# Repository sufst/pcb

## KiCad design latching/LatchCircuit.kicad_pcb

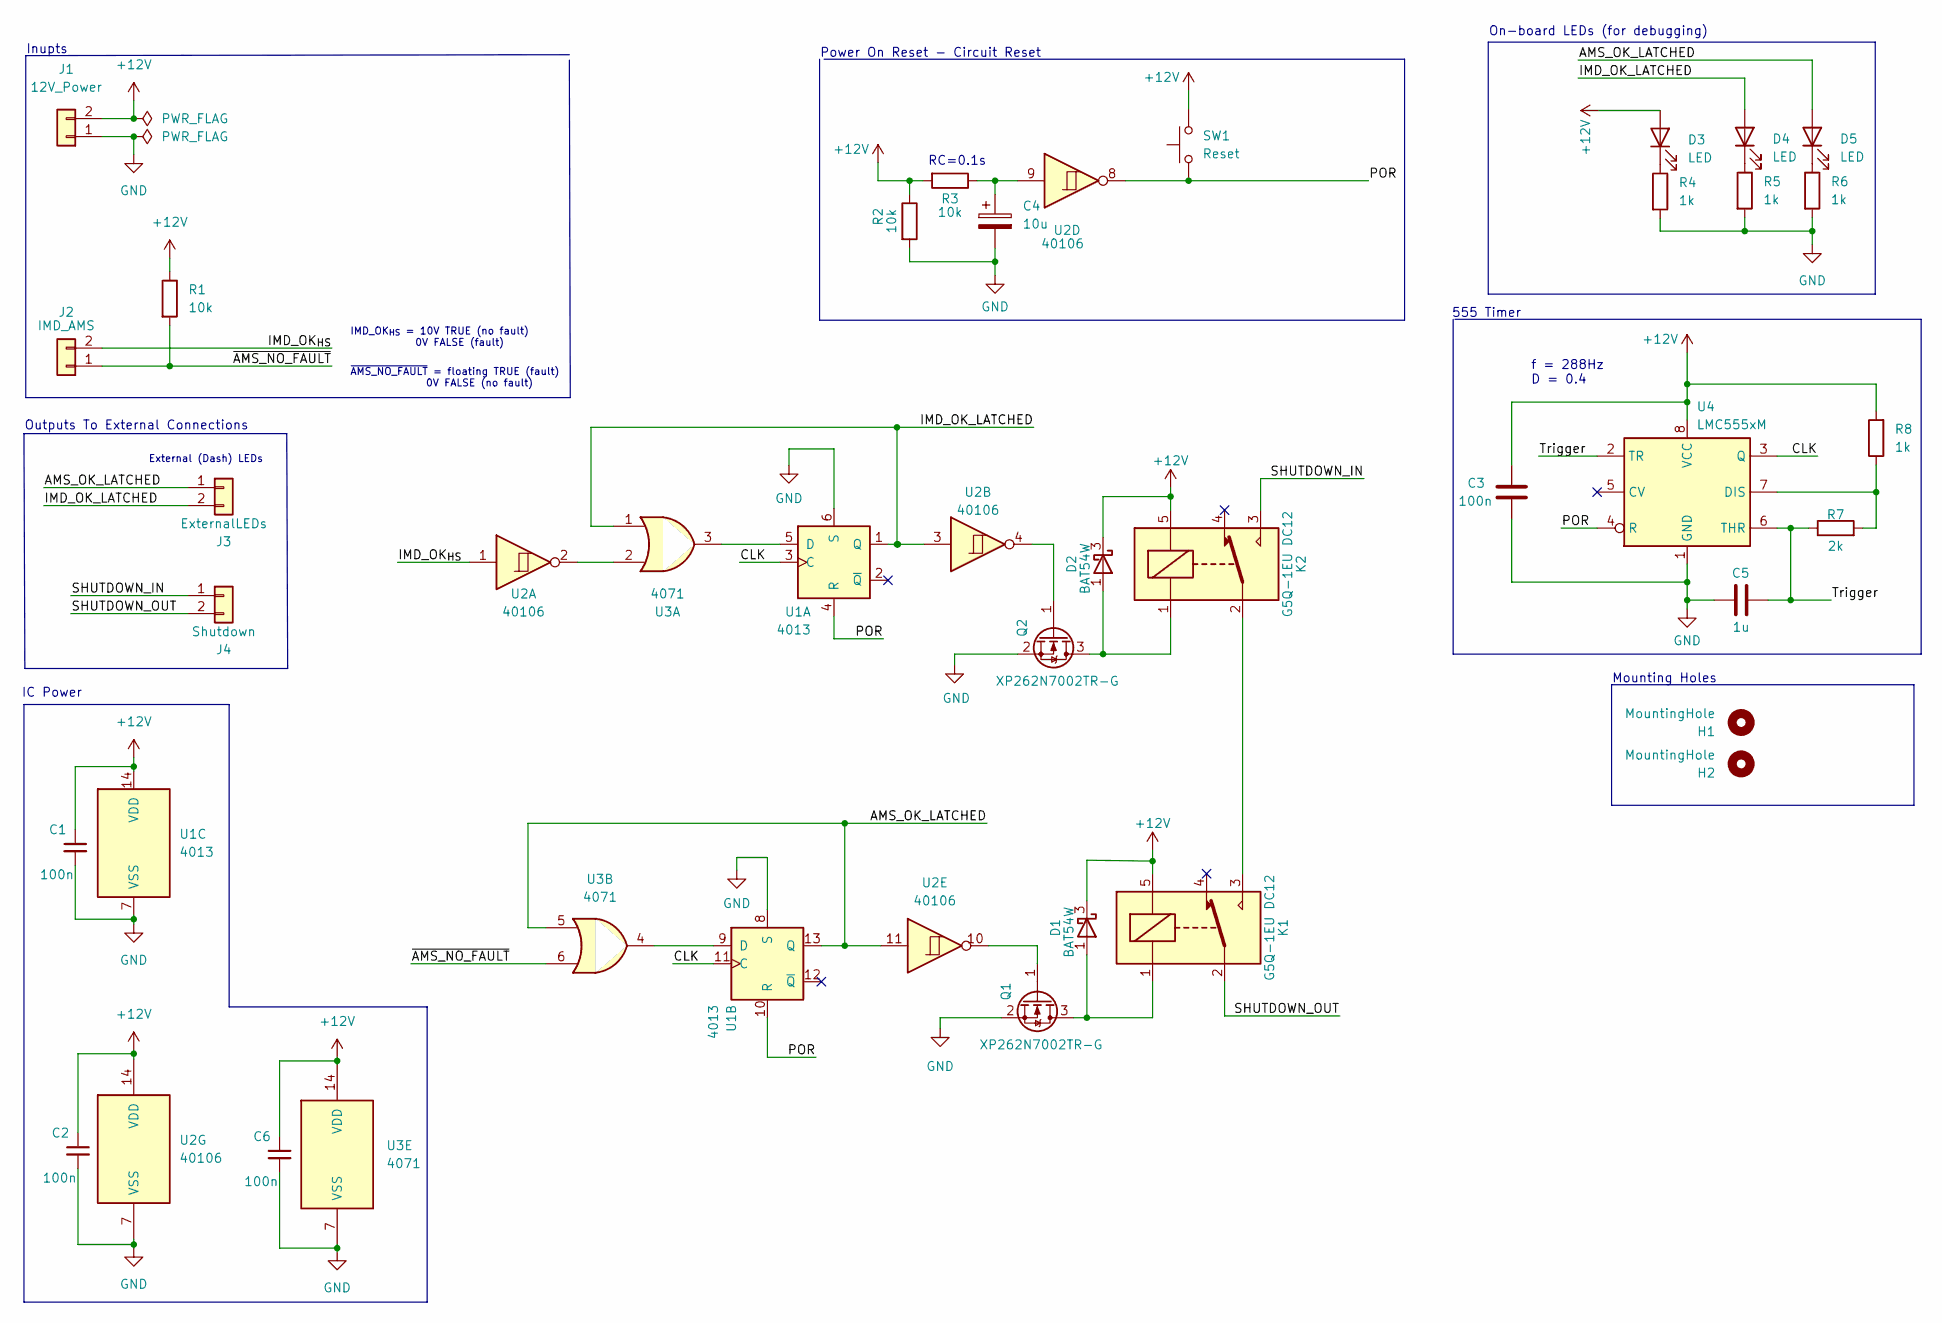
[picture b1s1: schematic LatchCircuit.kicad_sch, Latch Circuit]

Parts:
C1, C2, C3, C6: 100n; C_0603_1608Metric_Pad1.08x0.95mm_HandSolder
C4: 10u; CP_Radial_D5.0mm_P2.00mm
C5: 1u; CP_Radial_D5.0mm_P2.00mm
D1, D2: BAT54W; SOT-323_SC-70
D3, D4, D5: LED; LED_0805_2012Metric_Pad1.15x1.40mm_HandSolder
H1, H2: MountingHole; MountingHole_3.2mm_M3
J1: 12V_Power; Molex_Micro-Fit_3.0_43650-0200_1x02_P3.00mm_Horizontal
J2: IMD_AMS; Molex_Micro-Fit_3.0_43650-0200_1x02_P3.00mm_Horizontal
J3: ExternalLEDs; Molex_Micro-Fit_3.0_43650-0200_1x02_P3.00mm_Horizontal
J4: Shutdown; Molex_Micro-Fit_3.0_43650-0200_1x02_P3.00mm_Horizontal
K1, K2: G5Q-1EU DC12; Relay_SPDT_Omron-G5Q-1
Q1, Q2: XP262N7002TR-G; SOT-23
R1, R2, R3: 10k; R_0603_1608Metric_Pad0.98x0.95mm_HandSolder
R4, R5, R6, R8: 1k; R_0603_1608Metric_Pad0.98x0.95mm_HandSolder
R7: 2k; R_0603_1608Metric_Pad0.98x0.95mm_HandSolder
SW1: Reset; Molex_Micro-Fit_3.0_43650-0200_1x02_P3.00mm_Horizontal
U1: 4013; SOIC-14_3.9x8.7mm_P1.27mm
U2: 40106; SO-14_3.9x8.65mm_P1.27mm
U3: 4071; SOIC-14_3.9x8.7mm_P1.27mm
U4: LMC555xM; SOIC-8_3.9x4.9mm_P1.27mm

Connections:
+12V: C1.1, C2.1, C3.1, C6.1, D1.3 (K), D2.3 (K), D3.2 (A), J1.2, K1.5, K2.5, R1.1, R2.1, R3.2, R8.2, SW1.2, U1.14 (VDD), U2.14 (VDD), U3.14 (VDD), U4.8 (VCC)
/AMS_OK_LATCHED: D5.2 (A), J3.1, U1.13 (Q), U2.11, U3.5
/CLK: U1.3 (C), U1.11 (C), U4.3 (Q)
/IMD_OK_LATCHED: D4.2 (A), J3.2, U1.1 (Q), U2.3, U3.1
/IMD_OK_{HS}: J2.2, U2.1
/POR: SW1.1, U1.4 (R), U1.10 (R), U2.8, U4.4 (R)
/SHUTDOWN_IN: J4.1, K2.3
/SHUTDOWN_OUT: J4.2, K1.2
/Trigger: C5.2, R7.1, U4.2 (TR), U4.6 (THR)
/~AMS_NO_FAULT: J2.1, R1.2, U3.6
GND: C1.2, C2.2, C3.2, C4.2, C5.1, C6.2, J1.1, Q1.2 (S), Q2.2 (S), R2.2, R4.2, R5.2, R6.2, U1.6 (S), U1.7 (VSS), U1.8 (S), U2.7 (VSS), U3.7 (VSS), U4.1 (GND)
unnamed: C4.1, R3.1, U2.9
unnamed: D1.1 (A), K1.1, Q1.3 (D)
unnamed: D2.1 (A), K2.1, Q2.3 (D)
unnamed: D3.1 (K), R4.1
unnamed: D4.1 (K), R5.1
unnamed: D5.1 (K), R6.1
unnamed: K1.3, K2.2
unnamed: Q1.1 (G), U2.10
unnamed: Q2.1 (G), U2.4
unnamed: R7.2, R8.1, U4.7 (DIS)
unnamed: U1.5 (D), U3.3
unnamed: U1.9 (D), U3.4
unnamed: U2.2, U3.2

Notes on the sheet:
555 Timer
External (Dash) LEDs
IMD_OK_{HS} = 10V TRUE (no fault) 0V FALSE (fault)
On-board LEDs (for debugging)
Outputs To External Connections
~{AMS_NO_FAULT} = floating TRUE (fault) 0V FALSE (no fault)
IC Power
Mounting Holes
f = 288Hz D = 0.4
RC=0.1s
Inupts
Power On Reset - Circuit Reset

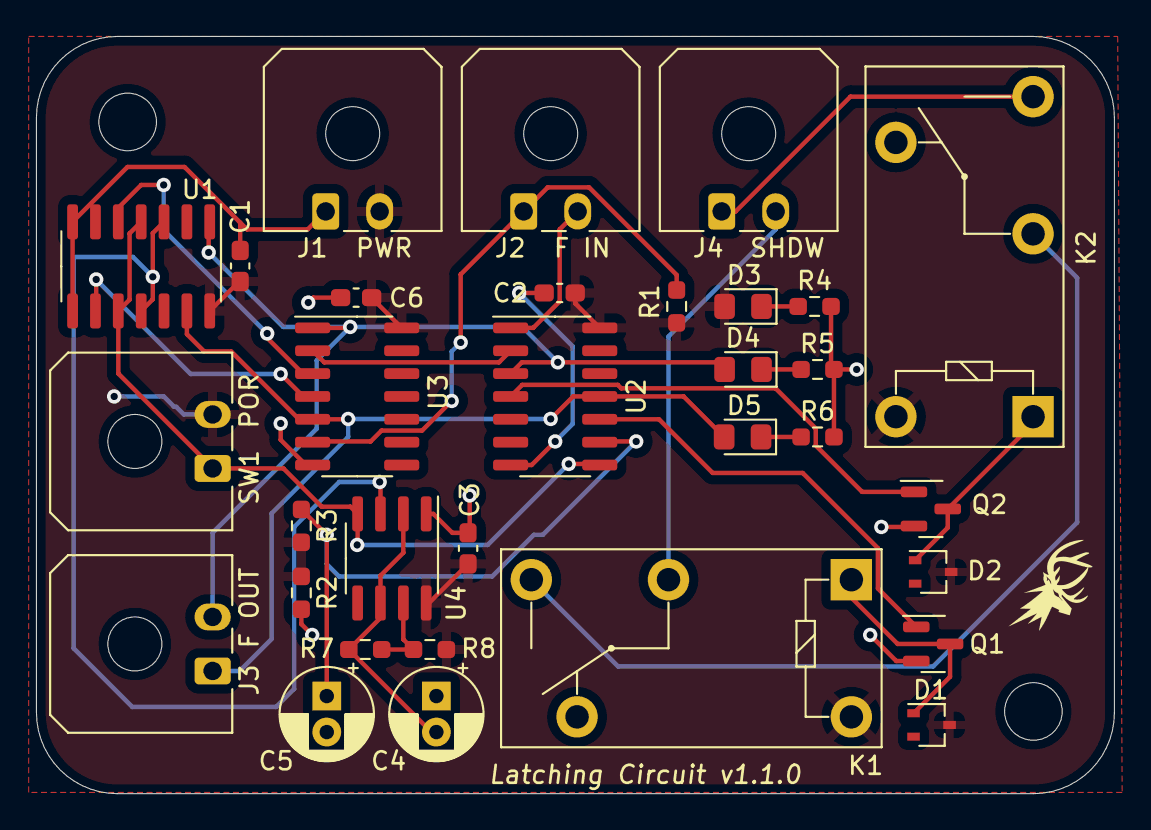
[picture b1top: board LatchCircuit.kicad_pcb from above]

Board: 2 copper layers, 59.9 x 42.1 mm, 34 parts (0 on the bottom side), 24 nets.

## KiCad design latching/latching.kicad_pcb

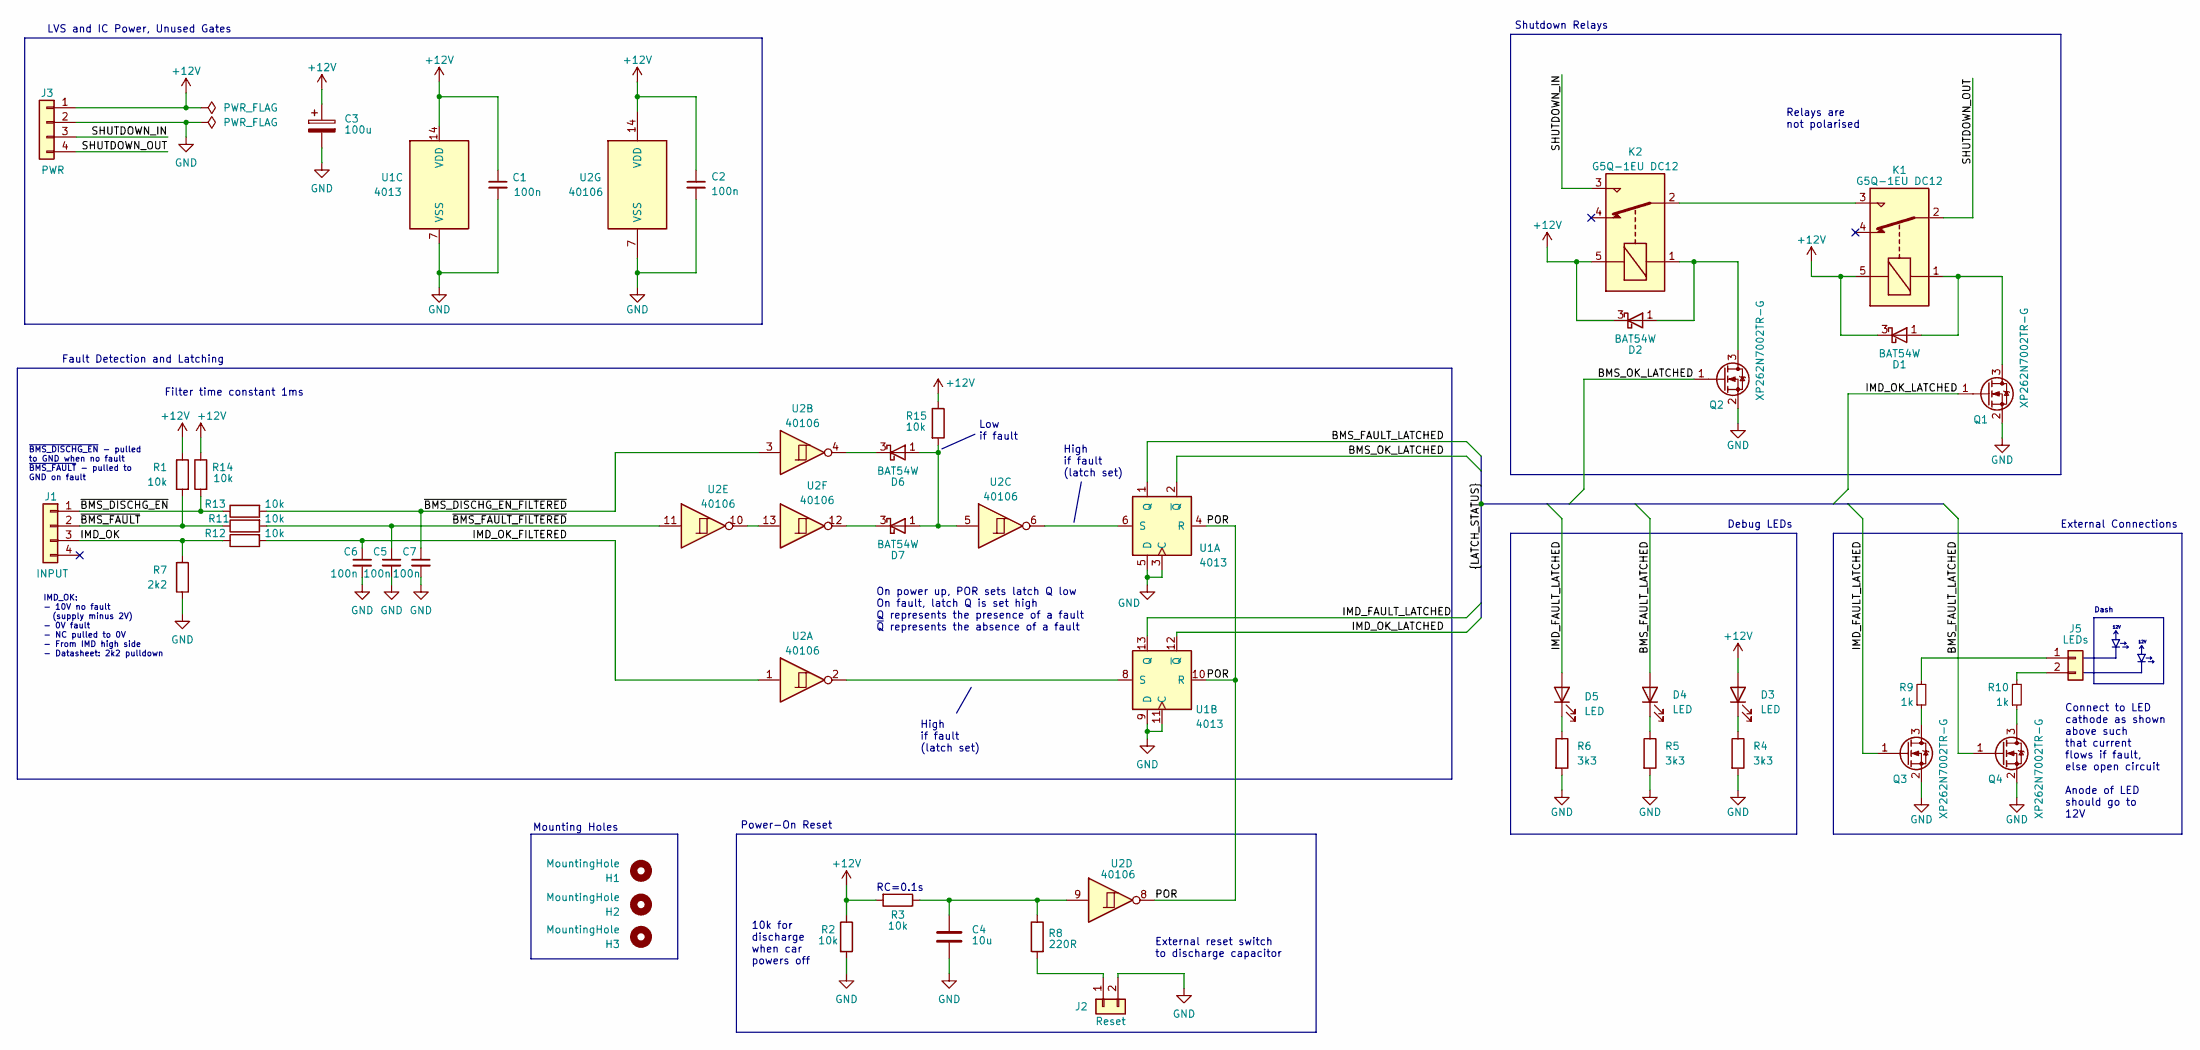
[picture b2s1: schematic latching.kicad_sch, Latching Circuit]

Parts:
C1, C2, C5, C6, C7: 100n; C_0805_2012Metric_Pad1.18x1.45mm_HandSolder
C3: 100u; CP_Radial_D5.0mm_P2.00mm
C4: 10u; C_0805_2012Metric_Pad1.18x1.45mm_HandSolder
D1, D2, D6, D7: BAT54W; SOT-323_SC-70
D3, D4, D5: LED; LED_0805_2012Metric_Pad1.15x1.40mm_HandSolder
H1, H2, H3: MountingHole; MountingHole_3.2mm_M3
J1: INPUT; Molex_Micro-Fit_3.0_43045-0400_2x02_P3.00mm_Horizontal
J2: Reset; Molex_Micro-Fit_3.0_43650-0200_1x02_P3.00mm_Horizontal
J3: PWR; Molex_Micro-Fit_3.0_43045-0400_2x02_P3.00mm_Horizontal
J5: LEDs; Molex_Micro-Fit_3.0_43650-0200_1x02_P3.00mm_Horizontal
K1, K2: G5Q-1EU DC12; Relay_SPDT_Omron-G5Q-1
Q1, Q2, Q3, Q4: XP262N7002TR-G; SOT-23
R1, R2, R3, R11, R12, R13, R14, R15: 10k; R_0805_2012Metric_Pad1.20x1.40mm_HandSolder
R4, R5, R6: 3k3; R_0805_2012Metric_Pad1.20x1.40mm_HandSolder
R7: 2k2; R_0805_2012Metric_Pad1.20x1.40mm_HandSolder
R8: 220R; R_0805_2012Metric_Pad1.20x1.40mm_HandSolder
R9, R10: 1k; R_0805_2012Metric_Pad1.20x1.40mm_HandSolder
U1: 4013; SOIC-14_3.9x8.7mm_P1.27mm
U2: 40106; SOIC-14_3.9x8.7mm_P1.27mm

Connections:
+12V: C1.1, C2.1, C3.1, D1.3 (K), D2.3 (K), D3.2 (A), J3.1, K1.5, K2.5, R1.1, R2.1, R3.2, R14.1, R15.1, U1.14 (VDD), U2.14 (VDD)
/BMS_FAULT_LATCHED: D4.2 (A), Q4.1 (G), U1.1 (Q)
/BMS_OK_LATCHED: Q2.1 (G), U1.2 (~Q)
/IMD_FAULT_LATCHED: D5.2 (A), Q3.1 (G), U1.13 (Q)
/IMD_OK: J1.3, R7.2, R12.1
/IMD_OK_FILTERED: C6.1, R12.2, U2.1
/IMD_OK_LATCHED: Q1.1 (G), U1.12 (~Q)
/POR: U1.4 (R), U1.10 (R), U2.8
/SHUTDOWN_IN: J3.3, K2.3
/SHUTDOWN_OUT: J3.4, K1.2
/~BMS_DISCHG_EN_FILTERED: C7.1, R13.2, U2.3
/~BMS_DISCHG_EN: J1.1, R13.1, R14.2
/~BMS_FAULT_FILTERED: C5.1, R11.2, U2.11
/~BMS_FAULT: J1.2, R1.2, R11.1
GND: C1.2, C2.2, C3.2, C4.2, C5.2, C6.2, C7.2, J2.2, J3.2, Q1.2 (S), Q2.2 (S), Q3.2 (S), Q4.2 (S), R2.2, R4.2, R5.2, R6.2, R7.1, U1.3 (C), U1.5 (D), U1.7 (VSS), U1.9 (D), U1.11 (C), U2.7 (VSS)
unnamed: C4.1, R3.1, R8.1, U2.9
unnamed: D1.1 (A), K1.1, Q1.3 (D)
unnamed: D2.1 (A), K2.1, Q2.3 (D)
unnamed: D3.1 (K), R4.1
unnamed: D4.1 (K), R5.1
unnamed: D5.1 (K), R6.1
unnamed: D6.1 (A), D7.1 (A), R15.2, U2.5
unnamed: D6.3 (K), U2.4
unnamed: D7.3 (K), U2.12
unnamed: J2.1, R8.2
unnamed: J5.1, R9.2
unnamed: J5.2, R10.2
unnamed: K1.3, K2.2
unnamed: Q3.3 (D), R9.1
unnamed: Q4.3 (D), R10.1
unnamed: U1.6 (S), U2.6
unnamed: U1.8 (S), U2.2
unnamed: U2.10, U2.13

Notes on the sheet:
High if fault (latch set)
Shutdown Relays
Connect to LED cathode as shown above such that current flows if fault, else open circuit Anode of LED should go to 12V
Power-On Reset
External Connections
IMD_OK: - 10V no fault (supply minus 2V) - 0V fault - NC pulled to 0V - From IMD high side - Datasheet: 2k2 pulldown
12V
High if fault (latch set)
Debug LEDs
10k for discharge when car powers off
Fault Detection and Latching
Low if fault
~{BMS_DISCHG_EN} - pulled to GND when no fault ~{BMS_FAULT} - pulled to GND on fault
Relays are not polarised
Mounting Holes
Dash
RC=0.1s
On power up, POR sets latch Q low On fault, latch Q is set high Q represents the presence of a fault ~{Q} represents the absence of a fault
LVS and IC Power, Unused Gates
External reset switch to discharge capacitor
Filter time constant 1ms

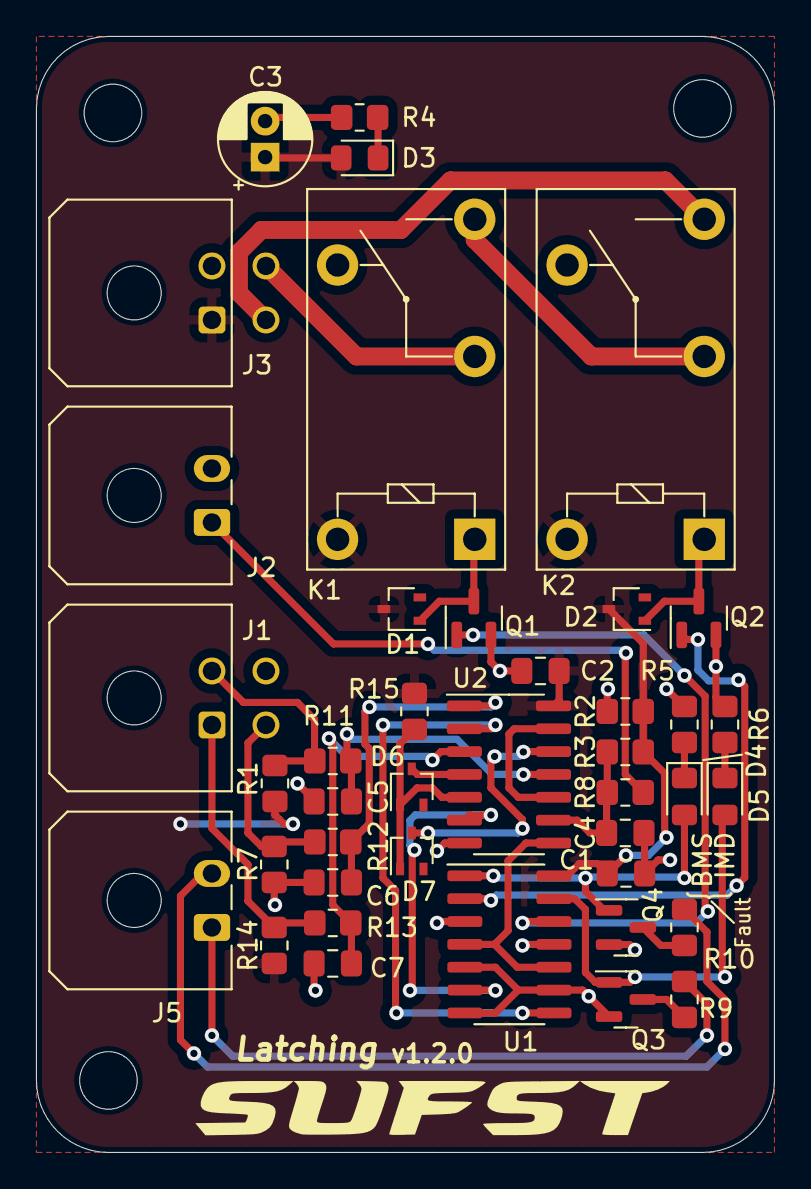
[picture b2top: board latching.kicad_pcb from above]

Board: 2 copper layers, 41.0 x 62.0 mm, 44 parts (0 on the bottom side), 33 nets.

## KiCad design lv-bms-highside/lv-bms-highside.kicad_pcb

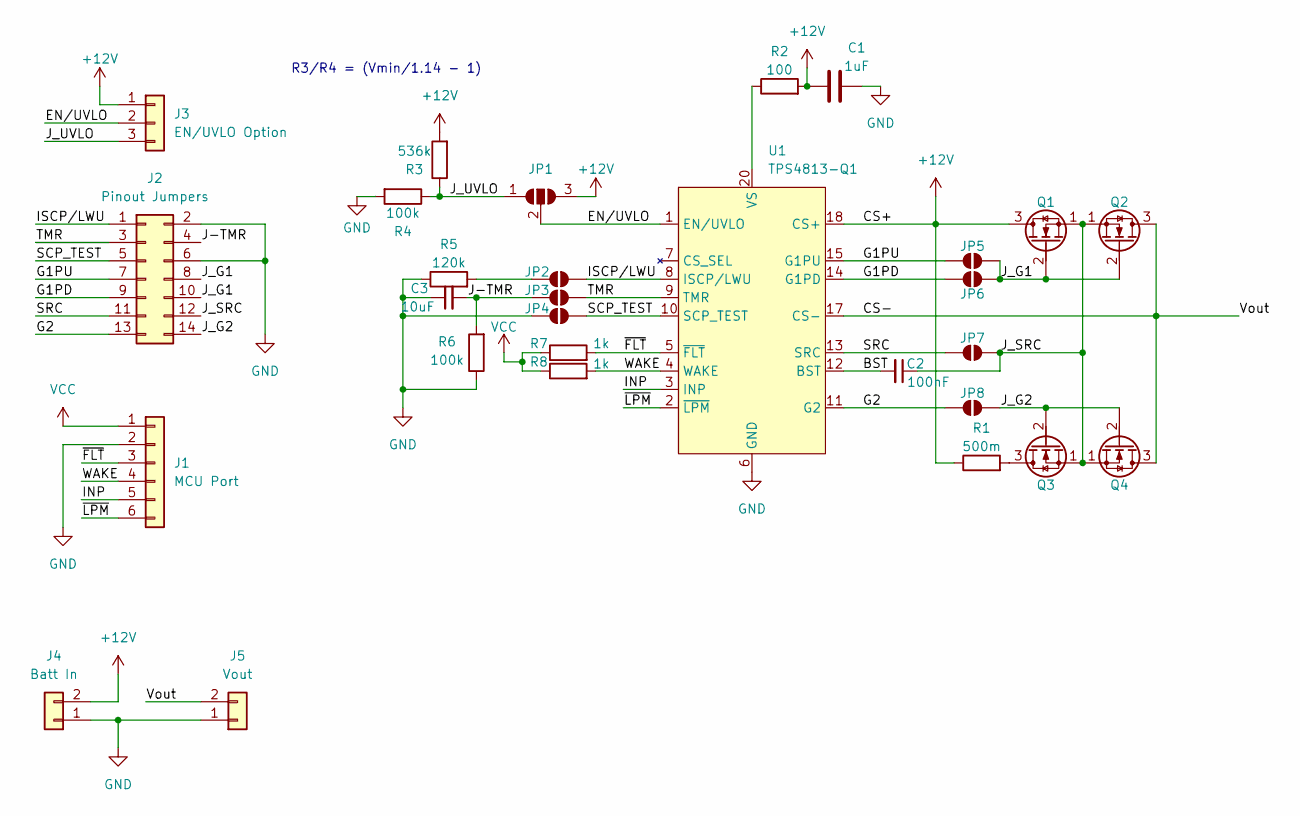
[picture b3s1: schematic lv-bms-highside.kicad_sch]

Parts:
C1: 1uF; C_0805_2012Metric
C2: 100nF; C_0805_2012Metric
C3: 10uF; C_0805_2012Metric
J1: MCU Port; PinHeader_1x06_P2.54mm_Vertical
J2: Pinout Jumpers; PinHeader_2x07_P2.54mm_Vertical
J3: EN/UVLO Option; PinHeader_1x03_P2.54mm_Vertical
J4: Batt In; TerminalBlock_Phoenix_MKDS-1,5-2-5.08_1x02_P5.08mm_Horizont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
J5: Vout; TerminalBlock_Phoenix_MKDS-1,5-2-5.08_1x02_P5.08mm_Horizont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
JP1: SolderJumper_3_Open; SolderJumper-3_P1.3mm_Open_RoundedPad1.0x1.5mm_NumberLabels
JP2, JP3, JP4, JP5, JP6, JP7, JP8: SolderJumper-2_P1.3mm_Open_RoundedPad1.0x1.5mm
Q1, Q2, Q3, Q4: Q_NMOS; DFN3333
R1: 500m; R_2512_6332Metric_Pad1.40x3.35mm_HandSolder
R2: 100; R_0805_2012Metric
R3: 536k; R_0805_2012Metric
R4, R6: 100k; R_0805_2012Metric
R5: 120k; R_0805_2012Metric
R7, R8: 1k; R_0805_2012Metric
U1: TPS4813-Q1; DGX0019A-MFG

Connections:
+12V: C1.2, J3.1, J4.2, JP1.3 (B), Q1.3 (D), R1.1, R2.2, R3.2, U1.18 (CS+)
/BST: C2.2, U1.12 (BST)
/CS-: J5.2, Q2.3 (D), Q4.3 (D), U1.17 (CS-)
/EN/UVLO: J3.2, JP1.2 (C), U1.1 (EN/UVLO)
/G1PD: J2.9, JP6.1 (A), U1.14 (G1PD)
/G1PU: J2.7, JP5.1 (A), U1.15 (G1PU)
/G2: J2.13, JP8.1 (A), U1.11 (G2)
/INP: J1.5, U1.3 (INP)
/ISCP/LWU: J2.1, JP2.2 (B), U1.8 (ISCP/LWU)
/J-TMR: C3.2, J2.4, JP3.1 (A), R6.2
/J_G1: J2.8, J2.10, JP5.2 (B), JP6.2 (B), Q1.2 (G), Q2.2 (G)
/J_G2: J2.14, JP8.2 (B), Q3.2 (G), Q4.2 (G)
/J_SRC: C2.1, J2.12, JP7.2 (B), Q1.1 (S), Q2.1 (S), Q3.1 (S), Q4.1 (S)
/J_UVLO: J3.3, JP1.1 (A), R3.1, R4.1
/SCP_TEST: J2.5, JP4.2 (B), U1.10 (SCP_TEST)
/SRC: J2.11, JP7.1 (A), U1.13 (SRC)
/TMR: J2.3, JP3.2 (B), U1.9 (TMR)
/WAKE: J1.4, R8.2, U1.4 (WAKE)
/~FLT: J1.3, R7.2, U1.5 (~FLT)
/~LPM: J1.6, U1.2 (~LPM)
GND: C1.1, C3.1, J1.2, J2.2, J2.6, J4.1, J5.1, JP4.1 (A), R4.2, R5.1, R6.1, U1.6 (GND)
unnamed: JP2.1 (A), R5.2
unnamed: Q3.3 (D), R1.2
unnamed: R2.1, U1.20 (VS)
VCC: J1.1, R7.1, R8.1

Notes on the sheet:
R3/R4 = (Vmin/1.14 - 1)

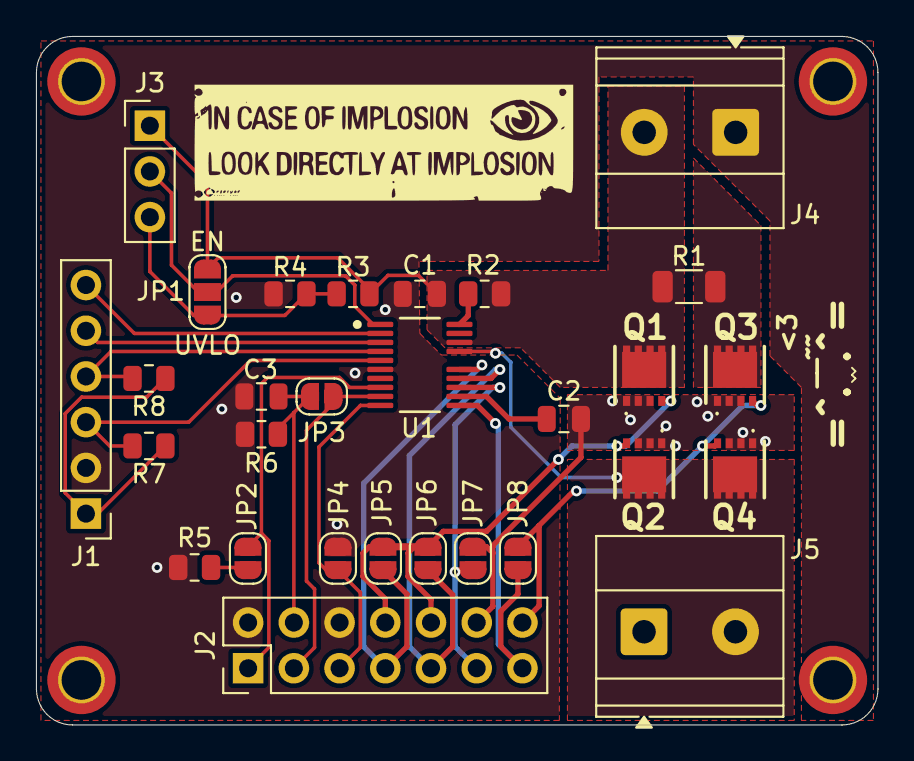
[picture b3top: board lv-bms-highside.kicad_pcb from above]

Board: 2 copper layers, 46.8 x 38.2 mm, 29 parts (0 on the bottom side), 25 nets.

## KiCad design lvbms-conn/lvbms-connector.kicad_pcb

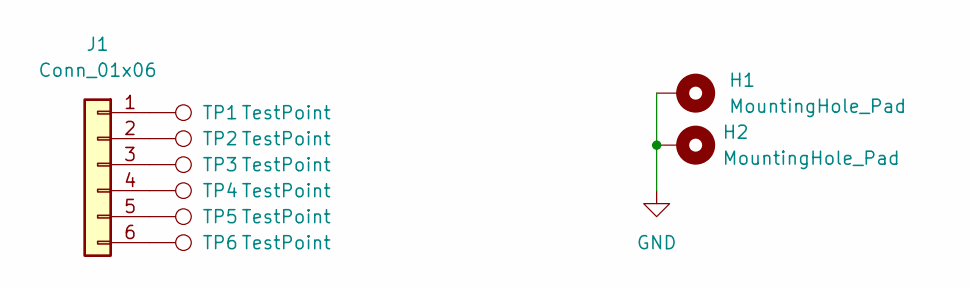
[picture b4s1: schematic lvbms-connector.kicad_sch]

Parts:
H1, H2: MountingHole_Pad; MountingHole_3.2mm_M3_DIN965_Pad_TopBottom
J1: Conn_01x06; Molex_Micro-Fit_3.0_43650-0600_1x06_P3.00mm_Horizontal
TP1, TP2, TP3, TP4, TP5, TP6: TestPoint; TestPoint_Pad_D1.0mm

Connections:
GND: H1.1, H2.1
unnamed: J1.1, TP1.1
unnamed: J1.2, TP2.1
unnamed: J1.3, TP3.1
unnamed: J1.4, TP4.1
unnamed: J1.5, TP5.1
unnamed: J1.6, TP6.1

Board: 2 copper layers, 9 parts (0 on the bottom side), 7 nets, no tracks yet.

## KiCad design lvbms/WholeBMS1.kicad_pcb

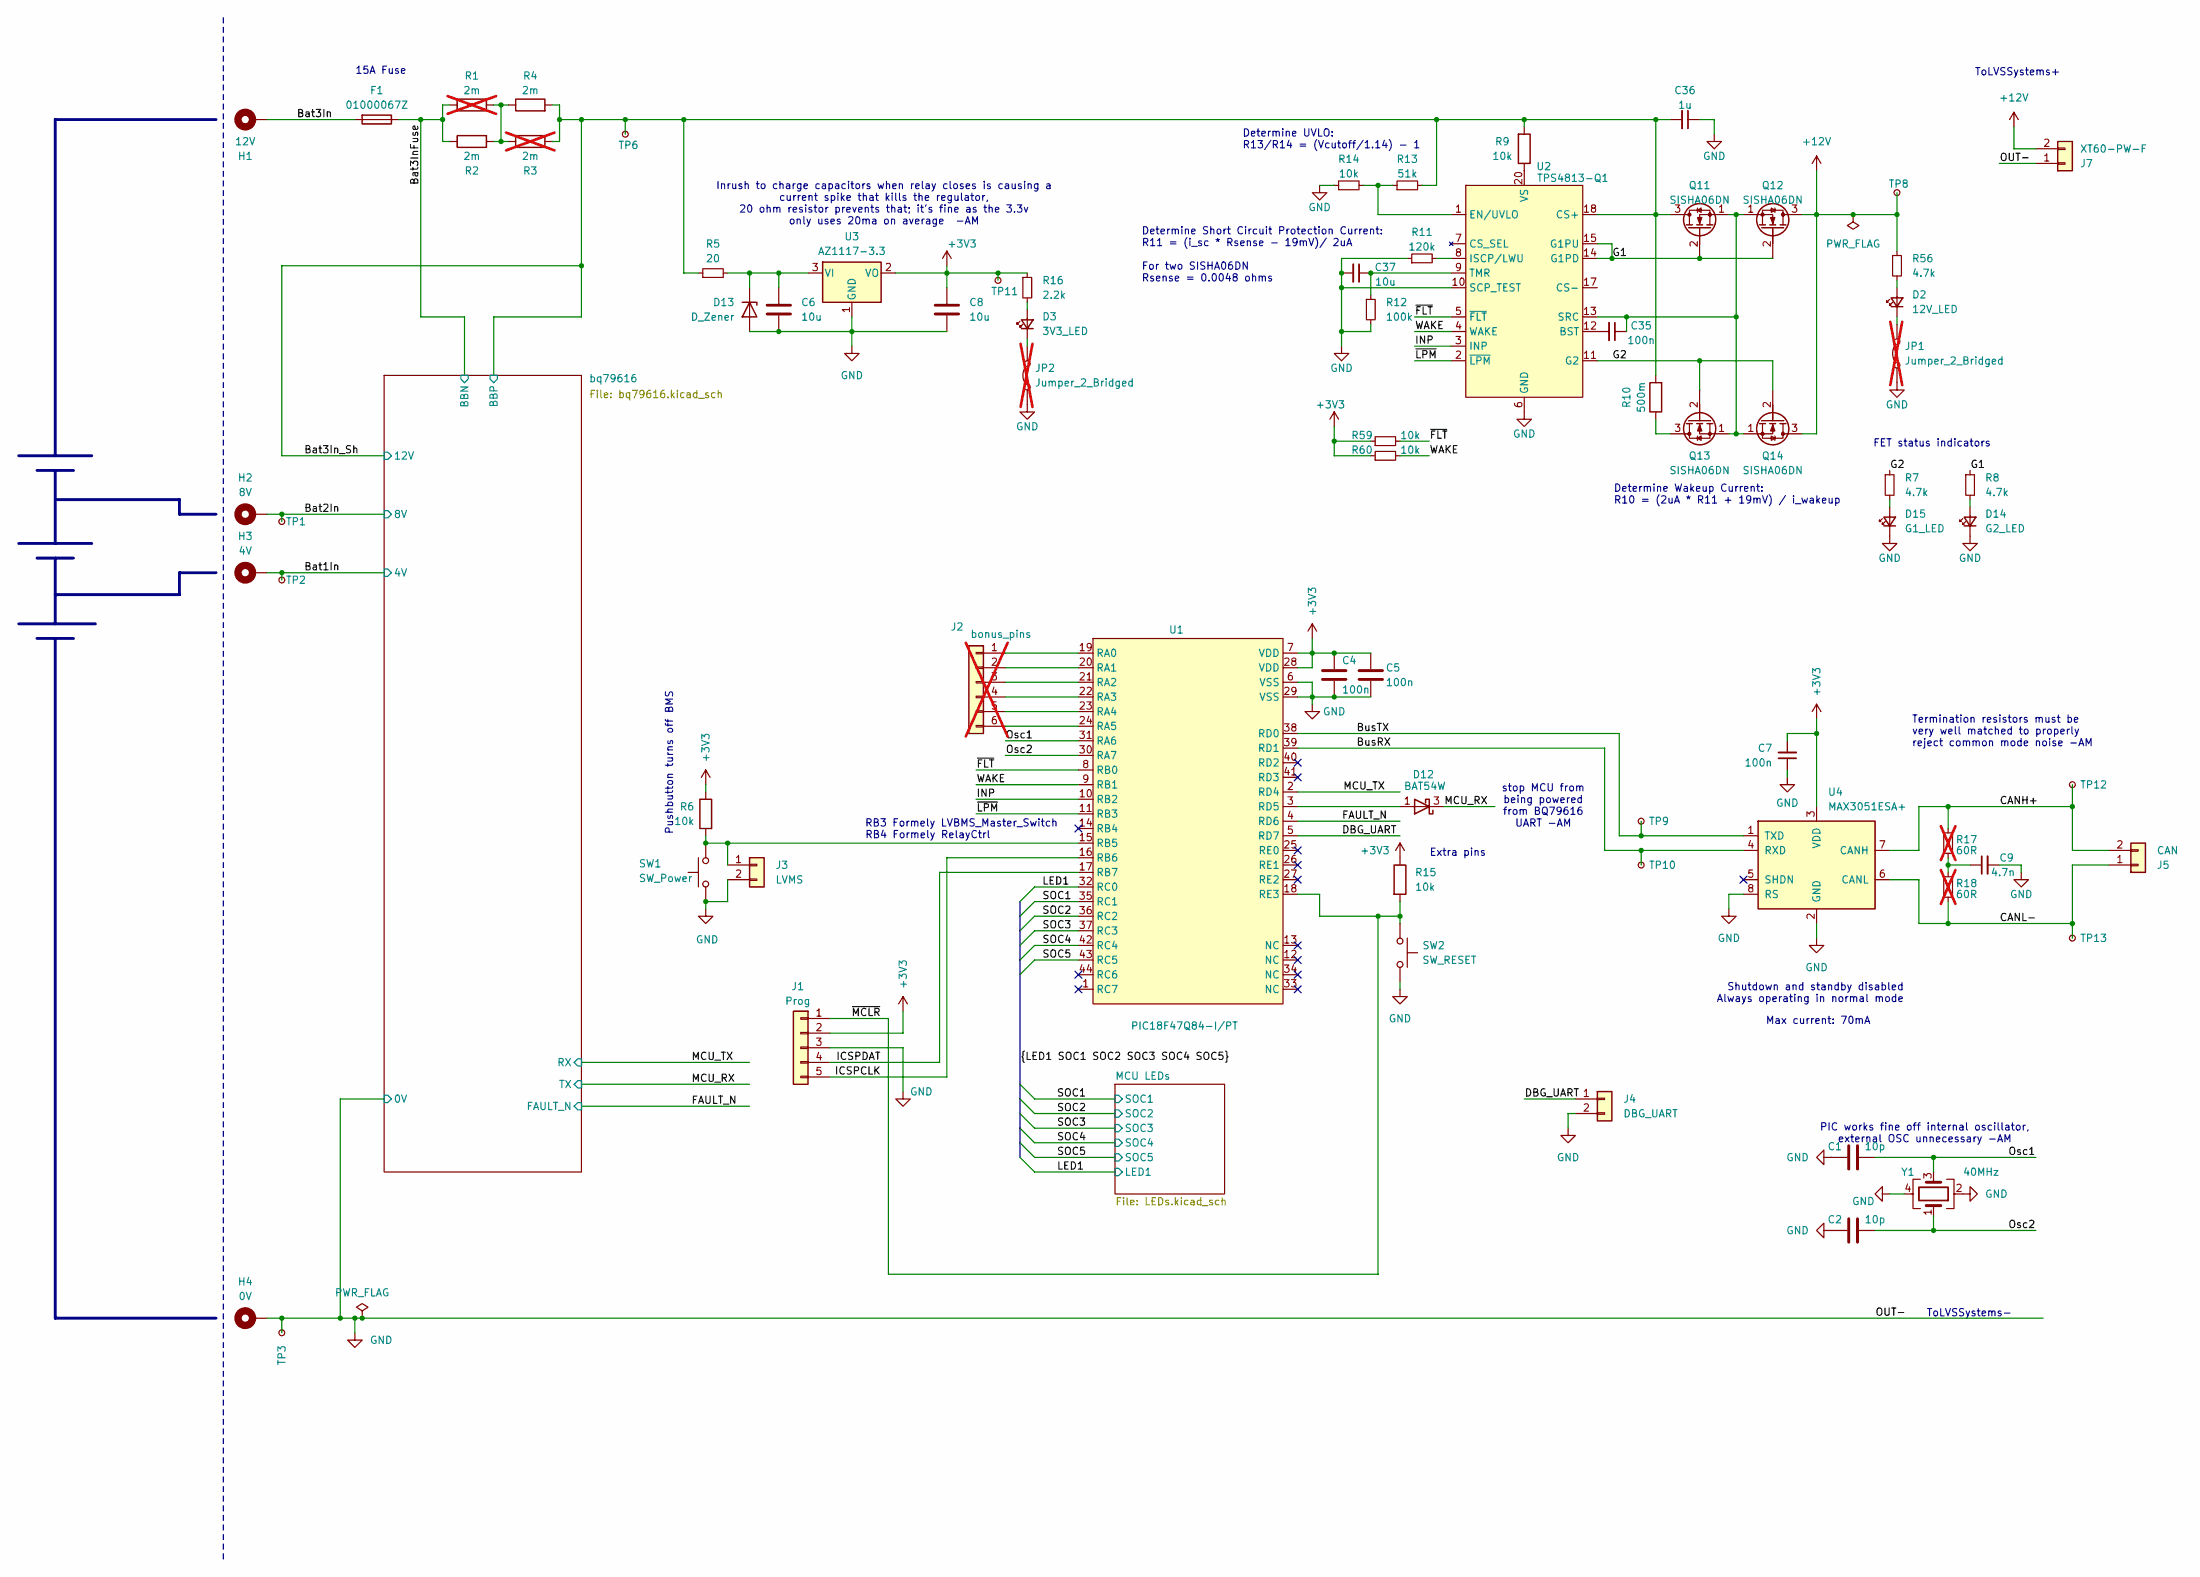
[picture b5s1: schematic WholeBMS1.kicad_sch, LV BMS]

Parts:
C1, C2: 10p; C_0603_1608Metric
C4, C5, C7, C35: 100n; C_0603_1608Metric
C6, C8, C37: 10u; C_0603_1608Metric
C9: 4.7n; C_0603_1608Metric
C36: 1u; C_0603_1608Metric
D2: 12V_LED; LED_0805_2012Metric_Pad1.15x1.40mm_HandSolder
D3: 3V3_LED; LED_0805_2012Metric_Pad1.15x1.40mm_HandSolder
D12: BAT54W; SOT-323_SC-70
D13: D_Zener; D_SOD-123
D14: G2_LED; LED_0805_2012Metric_Pad1.15x1.40mm_HandSolder
D15: G1_LED; LED_0805_2012Metric_Pad1.15x1.40mm_HandSolder
F1: 01000067Z; 01000060Z
H1: 12V; MountingHole_3.2mm_M3_Pad_TopBottom_with6mmClearanceForBMS
H2: 8V; MountingHole_3.2mm_M3_Pad_TopBottom_with6mmClearanceForBMS
H3: 4V; MountingHole_3.2mm_M3_Pad_TopBottom_with6mmClearanceForBMS
H4: 0V; MountingHole_3.2mm_M3_Pad_TopBottom_with6mmClearanceForBMS
J1: Prog; PinHeader_1x05_P2.54mm_Vertical
J2: bonus_pins; PinHeader_1x06_P2.54mm_Vertical; not fitted
J3: LVMS; Molex_Micro-Fit_3.0_43650-0200_1x02_P3.00mm_Horizontal
J4: DBG_UART; PinHeader_1x02_P2.54mm_Vertical
J5: CAN; Molex_Micro-Fit_3.0_43650-0200_1x02_P3.00mm_Horizontal
J7: XT60-PW-F; AMASS_XT60PW-F_1x02_P7.20mm_Horizontal
JP1, JP2: Jumper_2_Bridged; SolderJumper-2_P1.3mm_Bridged_RoundedPad1.0x1.5mm; not fitted
Q11, Q12, Q13, Q14: SISHA06DN; DFN3333
R1, R3: 2m; R_2512_6332Metric_Pad1.40x3.35mm_HandSolder; not fitted
R2, R4: 2m; R_2512_6332Metric_Pad1.40x3.35mm_HandSolder
R5: 20; R_0603_1608Metric
R6, R9, R14, R15, R59, R60: 10k; R_0603_1608Metric
R7, R8, R56: 4.7k; R_0603_1608Metric
R10: 500m; R_1210_3225Metric_Pad1.30x2.65mm_HandSolder
R11: 120k; R_0603_1608Metric
R12: 100k; R_0603_1608Metric
R13: 51k; R_0603_1608Metric
R16: 2.2k; R_0603_1608Metric
R17, R18: 60R; R_0603_1608Metric; not fitted
SW1: SW_Power; SW_Push_1P1T_NO_CK_KMR2
SW2: SW_RESET; SW_Push_1P1T_NO_CK_KMR2
TP1, TP2, TP3, TP6, TP8, TP9, TP10, TP11, TP12, TP13: TestPoint_Small; TestPoint_Pad_1.5x1.5mm
U1: PIC18F47Q84-I/PT; TQFP-44_10x10mm_P0.8mm
U2: TPS4813-Q1; DGX0019A-MFG
U3: AZ1117-3.3; SOT-223-3_TabPin2
U4: MAX3051ESA+; SOIC-8_3.9x4.9mm_P1.27mm
Y1: 40MHz; Crystal_SMD_SeikoEpson_FA128-4Pin_2.0x1.6mm

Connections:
+3V3: C4.1, C5.1, C7.2, C8.1, J1.2, R6.1, R15.1, R16.1, R59.1, R60.1, TP11.1, U1.7 (VDD), U1.28 (VDD), U3.2 (VO), U4.3 (VDD); also elsewhere on the board
+12V: J7.2, Q12.3 (D), Q14.3 (D), R56.1, TP8.1
/Bat1In: H3.1, TP2.1; also elsewhere on the board
/Bat2In: H2.1, TP1.1; also elsewhere on the board
/Bat3In: F1.2, H1.1
/Bat3InFuse: F1.1, R1.1, R2.1; also elsewhere on the board
/Bat3In_Sh: C36.2, Q11.3 (D), R3.2, R4.2, R5.1, R9.2, R10.2, R13.2, TP6.1, U2.18 (CS+); also elsewhere on the board
/BusRX: TP10.1, U1.39 (RD1), U4.4 (RXD)
/BusTX: TP9.1, U1.38 (RD0), U4.1 (TXD)
/CANH+: J5.2, R17.2, TP12.1, U4.7 (CANH)
/CANL-: J5.1, R18.1, TP13.1, U4.6 (CANL)
/DBG_UART: J4.1, U1.5 (RD7)
/FAULT_N: U1.4 (RD6); also elsewhere on the board
/G1: Q11.2 (G), Q12.2 (G), R8.1, U2.14 (G1PD), U2.15 (G1PU)
/G2: Q13.2 (G), Q14.2 (G), R7.1, U2.11 (G2)
/ICSPCLK: J1.5, U1.16 (RB6)
/ICSPDAT: J1.4, U1.17 (RB7)
/INP: U1.10 (RB2), U2.3 (INP)
/LED1: U1.32 (RC0); also elsewhere on the board
/MCU_RX: D12.3 (K); also elsewhere on the board
/MCU_TX: U1.2 (RD4); also elsewhere on the board
/Osc1: C1.2, U1.31 (RA6), Y1.3
/Osc2: C2.2, U1.30 (RA7), Y1.1
/SOC1: U1.35 (RC1); also elsewhere on the board
/SOC2: U1.36 (RC2); also elsewhere on the board
/SOC3: U1.37 (RC3); also elsewhere on the board
/SOC4: U1.42 (RC4); also elsewhere on the board
/SOC5: U1.43 (RC5); also elsewhere on the board
/WAKE: R60.2, U1.9 (RB1), U2.4 (WAKE)
/~FLT: R59.2, U1.8 (RB0), U2.5 (~FLT)
/~LPM: U1.11 (RB3), U2.2 (~LPM)
/~MCLR: J1.1, R15.2, SW2.1, U1.18 (RE3)
AVSS: C1.1, C2.1, C4.2, C5.2, C6.2, C7.1, C8.2, C9.2, C36.1, C37.2, D13.2 (A), D14.1 (K), D15.1 (K), H4.1, J1.3, J3.2, J4.2, J7.1, JP1.1 (A), JP2.1 (A), R11.1, R12.2, R14.1, SW1.2, SW2.2, TP3.1, U1.6 (VSS), U1.29 (VSS), U2.6 (GND), U2.10 (SCP_TEST), U3.1 (GND), U4.2 (GND), U4.8 (RS), Y1.2, Y1.4; also elsewhere on the board
unnamed: C9.1, R17.1, R18.2
unnamed: D2.2 (A), R56.2
unnamed: D2.1 (K), JP1.2 (B)
unnamed: D3.2 (A), R16.2
unnamed: D3.1 (K), JP2.2 (B)
unnamed: D12.1 (A), U1.3 (RD5)
unnamed: C6.1, D13.1 (K), R5.2, U3.3 (VI)
unnamed: D14.2 (A), R8.2
unnamed: D15.2 (A), R7.2
unnamed: J2.1, U1.19 (RA0)
unnamed: J2.2, U1.20 (RA1)
unnamed: J2.3, U1.21 (RA2)
unnamed: J2.4, U1.22 (RA3)
unnamed: J2.5, U1.23 (RA4)
unnamed: J2.6, U1.24 (RA5)
unnamed: J3.1, R6.2, SW1.1, U1.15 (RB5)
unnamed: C35.1, Q11.1 (S), Q12.1 (S), Q13.1 (S), Q14.1 (S), U2.13 (SRC)
unnamed: Q13.3 (D), R10.1
unnamed: R1.2, R2.2, R3.1, R4.1
unnamed: C35.2, U2.12 (BST)
unnamed: R13.1, R14.2, U2.1 (EN/UVLO)
unnamed: R11.2, U2.8 (ISCP/LWU)
unnamed: C37.1, R12.1, U2.9 (TMR)
unnamed: R9.1, U2.20 (VS)

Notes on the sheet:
Termination resistors must be very well matched to properly reject common mode noise -AM
Extra pins
RB3 Formely LVBMS_Master_Switch
Determine Wakeup Current: R10 = (2uA * R11 + 19mV) / i_wakeup
ToLVSSystems-
FET status indicators
Pushbutton turns off BMS
PIC works fine off internal oscillator, external OSC unnecessary -AM
Inrush to charge capacitors when relay closes is causing a current spike that kills the regulator, 20 ohm resistor prevents that; it's fine as the 3.3v only uses 20ma on average -AM
ToLVSSystems+
Max current: 70mA
Determine Short Circuit Protection Current: R11 = (i_sc * Rsense - 19mV)/ 2uA For two SISHA06DN Rsense = 0.0048 ohms
Determine UVLO: R13/R14 = (Vcutoff/1.14) - 1
Shutdown and standby disabled Always operating in normal mode
stop MCU from being powered from BQ79616 UART -AM
RB4 Formely RelayCtrl
15A Fuse

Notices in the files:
parts and their libraries:
License: Apache-2.0
